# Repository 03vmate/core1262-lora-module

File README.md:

# core1262-lora-module
Schematics and layout for Waveshare Core1262 LoRA breakout board/module

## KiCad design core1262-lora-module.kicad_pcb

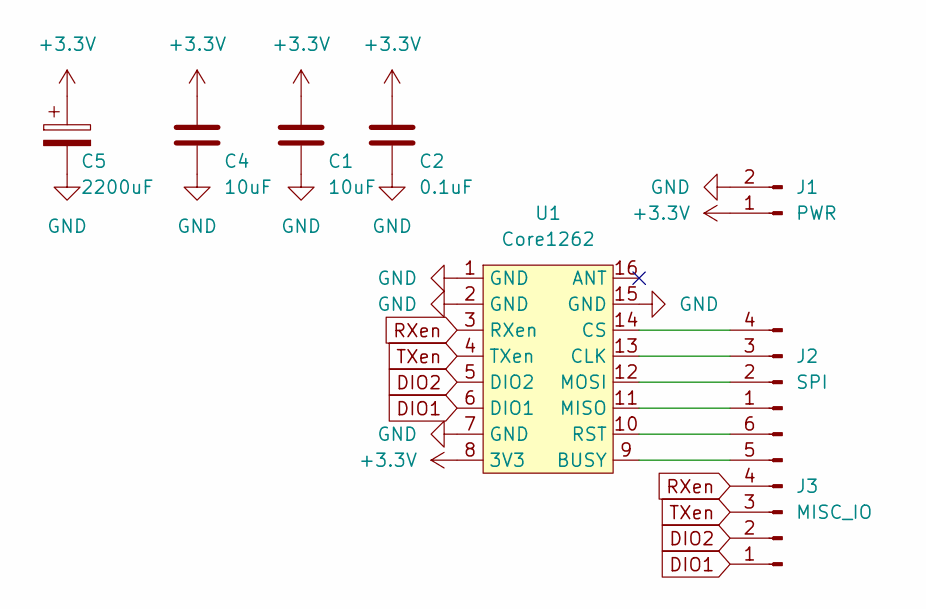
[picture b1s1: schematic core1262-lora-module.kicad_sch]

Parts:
C1, C4: 10uF; C_0805_2012Metric
C2: 0.1uF; C_0805_2012Metric
C5: 2200uF; CP_Radial_D10.0mm_P5.00mm
J1: PWR; JST_PH_B2B-PH-K_1x02_P2.00mm_Vertical
J2: SPI; JST_PH_B4B-PH-K_1x04_P2.00mm_Vertical
J3: MISC_IO; JST_PH_B6B-PH-K_1x06_P2.00mm_Vertical
U1: Core1262

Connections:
+3.3V: C1.1, C2.1, C4.1, C5.1, J1.1, U1.8 (3V3)
DIO1: J3.1, U1.6 (DIO1)
DIO2: J3.2, U1.5 (DIO2)
GND: C1.2, C2.2, C4.2, C5.2, J1.2, U1.1 (GND), U1.2 (GND), U1.7 (GND), U1.15 (GND)
unnamed: J2.1, U1.11 (MISO)
unnamed: J2.2, U1.12 (MOSI)
unnamed: J2.3, U1.13 (CLK)
unnamed: J2.4, U1.14 (CS)
unnamed: J3.5, U1.9 (BUSY)
unnamed: J3.6, U1.10 (RST)
RXen: J3.4, U1.3 (RXen)
TXen: J3.3, U1.4 (TXen)

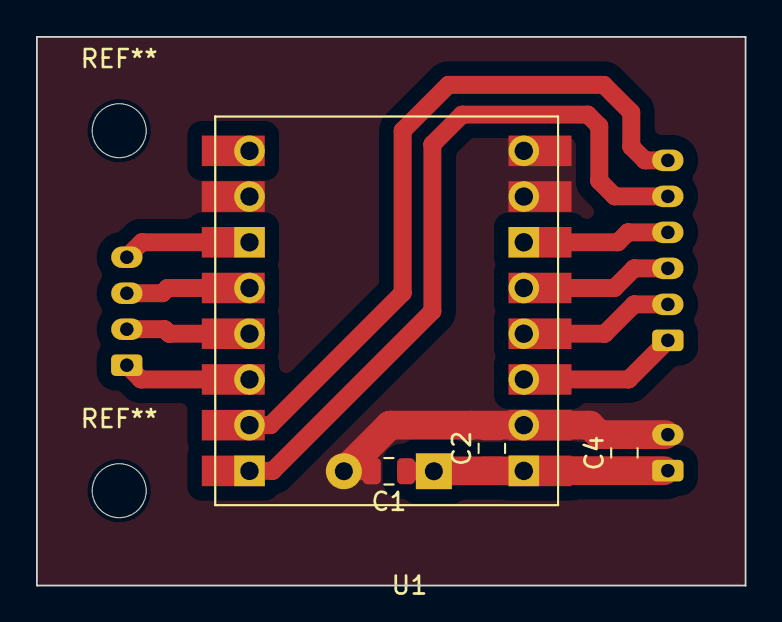
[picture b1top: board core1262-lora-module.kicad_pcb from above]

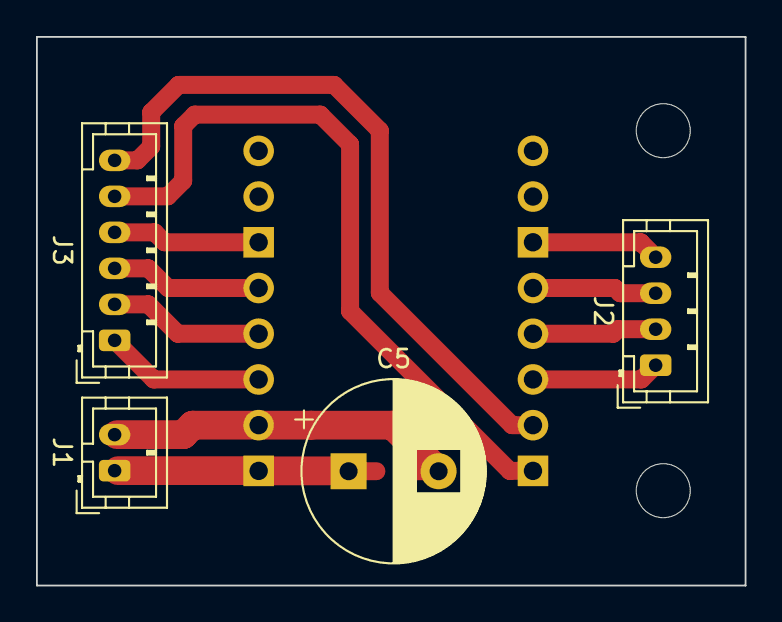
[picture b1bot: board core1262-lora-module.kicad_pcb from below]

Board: 2 copper layers, 39.4 x 30.5 mm, 8 parts (4 on the bottom side), 12 nets.

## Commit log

2024-01-06 Create KiCad project and Core1262 symbol+footprint
2024-01-06 Schematic
2024-01-06 Include Core1262 module .mod and .sym
2024-01-06 Footprint assignments
2024-01-06 Fix Core1262 pin numbering
2024-01-06 PCB layout
